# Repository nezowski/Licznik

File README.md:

# Licznik
Licznik odliczajacy liczbe dni do wakacji

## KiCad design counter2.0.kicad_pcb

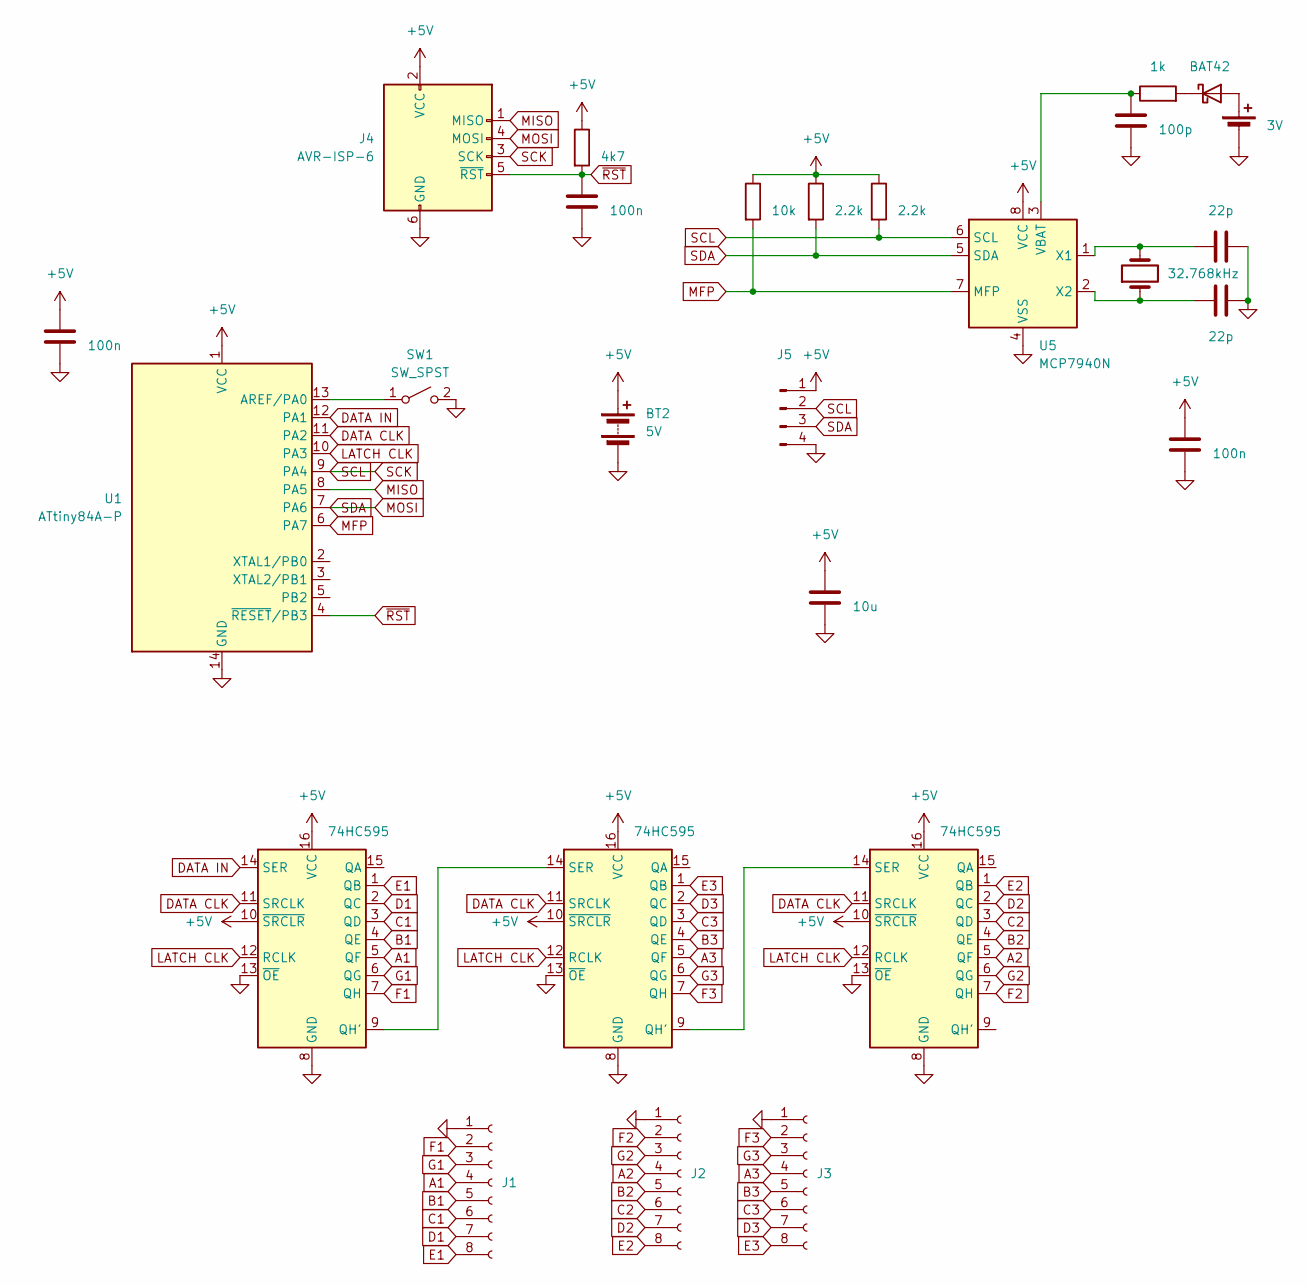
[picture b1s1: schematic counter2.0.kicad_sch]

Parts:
BT1: 3V; BatteryHolder_Keystone_105_1x2430
BT2: 5V; PinHeader_1x02_P2.54mm_Vertical
C1, C2: 22p; C_Disc_D3.0mm_W1.6mm_P2.50mm
C3, C5, C7: 100n; C_Disc_D3.0mm_W1.6mm_P2.50mm
C4: 100p; C_Disc_D3.0mm_W1.6mm_P2.50mm
C6: 10u; C_Radial_D6.3mm_H5.0mm_P2.50mm
D1: BAT42; D_DO-35_SOD27_P7.62mm_Horizontal
J1, J2, J3: Conn_01x08_Socket; PinSocket_1x08_P2.54mm_Vertical
J4: AVR-ISP-6; IDC-Header_2x03_P2.54mm_Vertical
J5: Conn_01x04_Pin; PinHeader_1x04_P2.54mm_Vertical
R1, R2: 2.2k; R_Axial_DIN0207_L6.3mm_D2.5mm_P7.62mm_Horizontal
R3: 10k; R_Axial_DIN0207_L6.3mm_D2.5mm_P7.62mm_Horizontal
R4: 1k; R_Axial_DIN0207_L6.3mm_D2.5mm_P7.62mm_Horizontal
R5: 4k7; R_Axial_DIN0207_L6.3mm_D2.5mm_P7.62mm_Horizontal
SW1: SW_SPST; PinHeader_1x02_P2.54mm_Vertical
U1: ATtiny84A-P; DIP-14_W7.62mm
U2, U3, U4: 74HC595; DIP-16_W7.62mm
U5: MCP7940N; DIP-8_W7.62mm
Y1: 32.768kHz; Crystal_AT310_D3.0mm_L10.0mm_Vertical

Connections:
+5V: BT2.1 (+), C3.1, C5.1, C6.1, J4.2 (VCC), J5.1, R1.1, R2.1, R3.1, R5.1, U1.1 (VCC), U2.10 (~SRCLR), U2.16 (VCC), U3.10 (~SRCLR), U3.16 (VCC), U4.10 (~SRCLR), U4.16 (VCC), U5.8 (VCC)
A1: J1.4, U2.5 (QF)
A2: J2.4, U4.5 (QF)
A3: J3.4, U3.5 (QF)
B1: J1.5, U2.4 (QE)
B2: J2.5, U4.4 (QE)
B3: J3.5, U3.4 (QE)
C1: J1.6, U2.3 (QD)
C2: J2.6, U4.3 (QD)
C3: J3.6, U3.3 (QD)
D1: J1.7, U2.2 (QC)
D2: J2.7, U4.2 (QC)
D3: J3.7, U3.2 (QC)
DATA CLK: U1.11 (PA2), U2.11 (SRCLK), U3.11 (SRCLK), U4.11 (SRCLK)
DATA IN: U1.12 (PA1), U2.14 (SER)
E1: J1.8, U2.1 (QB)
E2: J2.8, U4.1 (QB)
E3: J3.8, U3.1 (QB)
F1: J1.2, U2.7 (QH)
F2: J2.2, U4.7 (QH)
F3: J3.2, U3.7 (QH)
G1: J1.3, U2.6 (QG)
G2: J2.3, U4.6 (QG)
G3: J3.3, U3.6 (QG)
GND: BT1.2 (-), BT2.2 (-), C1.2, C2.2, C3.2, C4.2, C5.2, C6.2, C7.2, J1.1, J2.1, J3.1, J4.6 (GND), J5.4, SW1.2 (B), U1.14 (GND), U2.8 (GND), U2.13 (~OE), U3.8 (GND), U3.13 (~OE), U4.8 (GND), U4.13 (~OE), U5.4 (VSS)
LATCH CLK: U1.10 (PA3), U2.12 (RCLK), U3.12 (RCLK), U4.12 (RCLK)
MFP: R3.2, U1.6 (PA7), U5.7 (MFP)
MISO: J4.1 (MISO), U1.8 (PA5)
MOSI: J4.4 (MOSI), J5.3, R2.2, U1.7 (PA6), U5.5 (SDA)
unnamed: BT1.1 (+), D1.2 (A)
unnamed: D1.1 (K), R4.2
unnamed: SW1.1 (A), U1.13 (AREF/PA0)
unnamed: U2.9 (QH'), U3.14 (SER)
unnamed: U3.9 (QH'), U4.14 (SER)
unnamed: C4.1, R4.1, U5.3 (VBAT)
unnamed: C1.1, U5.1 (X1), Y1.2
unnamed: C2.1, U5.2 (X2), Y1.1
SCK: J4.3 (SCK), J5.2, R1.2, U1.9 (PA4), U5.6 (SCL)
~RST: C7.1, J4.5 (~RST), R5.2, U1.4 (~RESET/PB3)

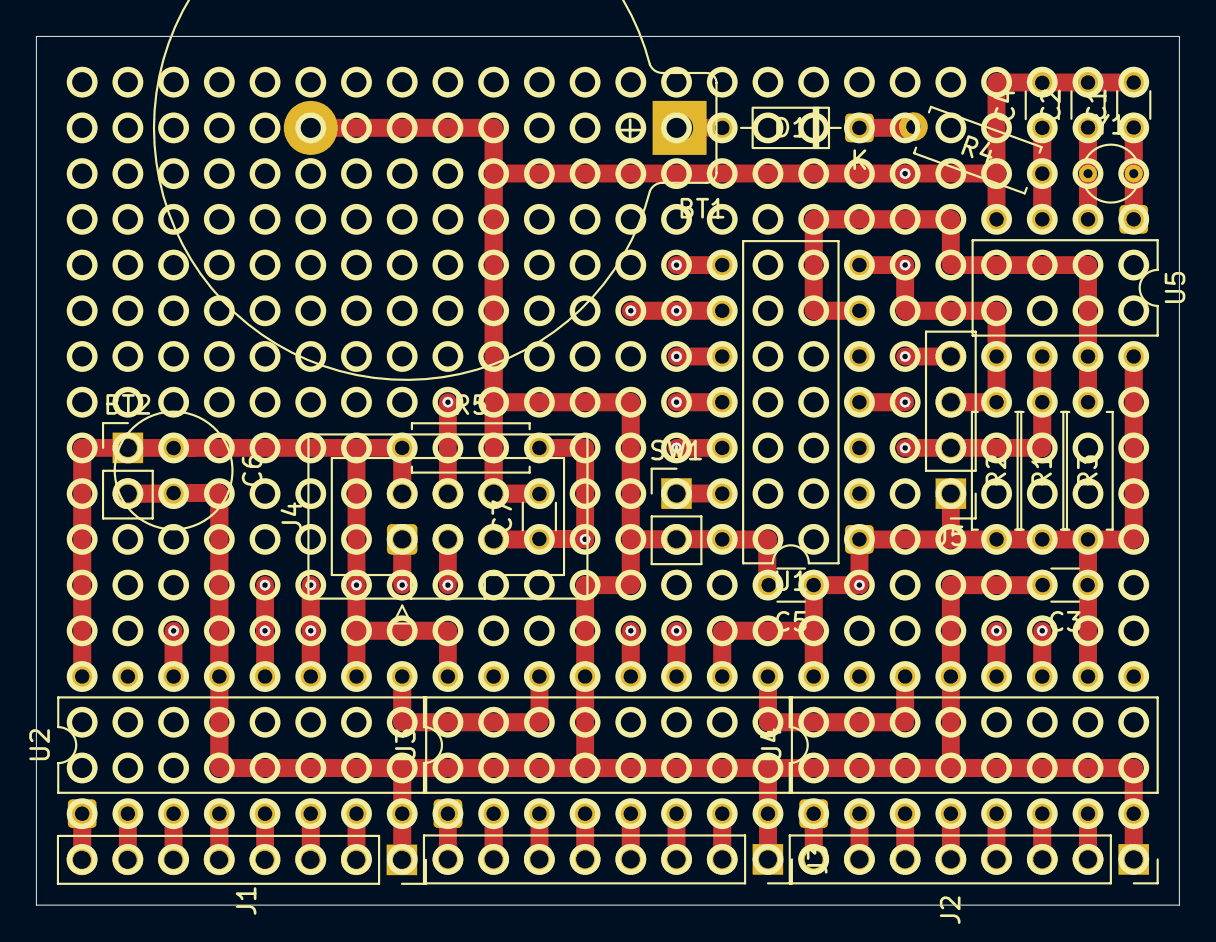
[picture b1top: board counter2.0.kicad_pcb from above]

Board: 6 copper layers, 63.5 x 48.3 mm, 28 parts (0 on the bottom side), 39 nets.

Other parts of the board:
REFe: 50x70mm

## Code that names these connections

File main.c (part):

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#include <avr/sleep.h>
#include <util/delay.h>

#define ONOFFSWITCH PA0
#define DATAIN PA1
#define DATACLK PA2
#define LATCHCLK PA3
#define SCL PA4
#define SDA PA6
#define MFP PA7

#define MCP_ADDR 0x6F << 1
#define READ 1
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
		sleep_mode();

		if (!(PINA & (1<<MFP))) {		// MFP 0 - interrupt
			//handle mfp interrupt

			// since interrupts on mcp7940 will be fired till matching event stops, we cant just set one alarm to 1:00 everyday
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
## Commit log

2025-09-10 Rename counter2.0.kicad_sch to kicad/counter.kicad_sch
2025-09-10 Rename counter2.0.kicad_pcb to counter.kicad_pcb
2025-09-10 Rename counter2.0.kicad_pro to counter.kicad_pro
2025-09-10 Rename counter2.0.kicad_prl to counter.kicad_prl
